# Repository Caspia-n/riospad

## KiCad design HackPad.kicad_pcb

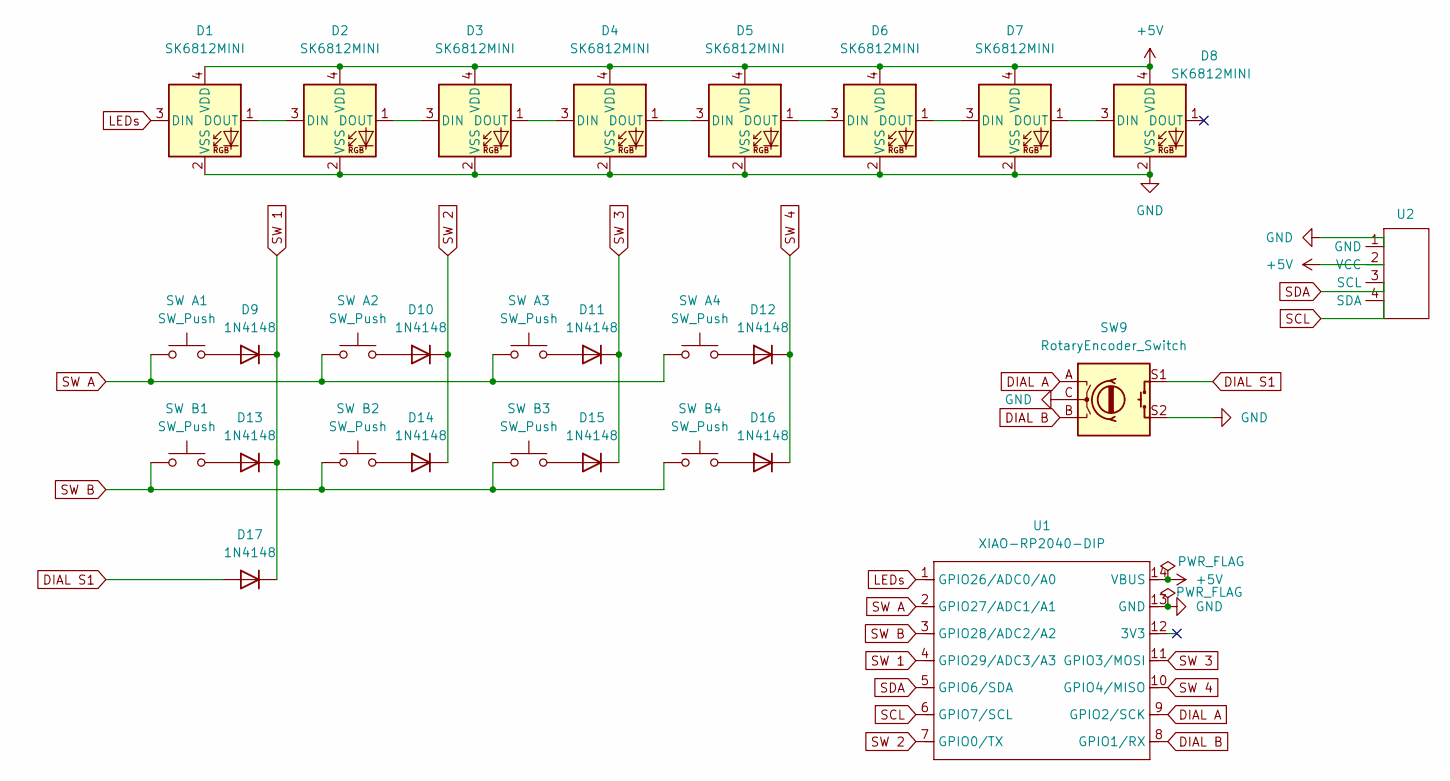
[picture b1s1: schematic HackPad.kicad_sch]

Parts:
D1, D2, D3, D4, D5, D6, D7, D8: SK6812MINI; LED_SK6812MINI_PLCC4_3.5x3.5mm_P1.75mm
D9, D10, D11, D12, D13, D14, D15, D16, D17: 1N4148; D_DO-35_SOD27_P7.62mm_Horizontal
SW9: RotaryEncoder_Switch; RotaryEncoder_Alps_EC12E-Switch_Vertical_H20mm
SW A1, SW A2, SW A3, SW A4: SW_Push; SW_Cherry_MX_1.00u_PCB
SW B1, SW B2, SW B3, SW B4: SW_Push; SW_Cherry_MX_1.00u_PCB
U1: XIAO-RP2040-DIP
U2: SSD1306-0.91-OLED-4pin-128x32

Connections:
+5V: D1.4 (VDD), D2.4 (VDD), D3.4 (VDD), D4.4 (VDD), D5.4 (VDD), D6.4 (VDD), D7.4 (VDD), D8.4 (VDD), U1.14 (VBUS), U2.2 (VCC)
DIAL A: SW9.A, U1.9 (GPIO2/SCK)
DIAL B: SW9.B, U1.8 (GPIO1/RX)
DIAL S1: D17.2 (A), SW9.S1
GND: D1.2 (VSS), D2.2 (VSS), D3.2 (VSS), D4.2 (VSS), D5.2 (VSS), D6.2 (VSS), D7.2 (VSS), D8.2 (VSS), SW9.C, SW9.S2, U1.13 (GND), U2.1 (GND)
LEDs: D1.3 (DIN), U1.1 (GPIO26/ADC0/A0)
unnamed: D1.1 (DOUT), D2.3 (DIN)
unnamed: D2.1 (DOUT), D3.3 (DIN)
unnamed: D3.1 (DOUT), D4.3 (DIN)
unnamed: D4.1 (DOUT), D5.3 (DIN)
unnamed: D5.1 (DOUT), D6.3 (DIN)
unnamed: D6.1 (DOUT), D7.3 (DIN)
unnamed: D7.1 (DOUT), D8.3 (DIN)
unnamed: D9.2 (A), SW A1.2
unnamed: D10.2 (A), SW A2.2
unnamed: D11.2 (A), SW A3.2
unnamed: D12.2 (A), SW A4.2
unnamed: D13.2 (A), SW B1.2
unnamed: D14.2 (A), SW B2.2
unnamed: D15.2 (A), SW B3.2
unnamed: D16.2 (A), SW B4.2
SCL: U1.6 (GPIO7/SCL), U2.4 (SDA)
SDA: U1.5 (GPIO6/SDA), U2.3 (SCL)
SW 1: D9.1 (K), D13.1 (K), D17.1 (K), U1.4 (GPIO29/ADC3/A3)
SW 2: D10.1 (K), D14.1 (K), U1.7 (GPIO0/TX)
SW 3: D11.1 (K), D15.1 (K), U1.11 (GPIO3/MOSI)
SW 4: D12.1 (K), D16.1 (K), U1.10 (GPIO4/MISO)
SW A: SW A1.1, SW A2.1, SW A3.1, SW A4.1, U1.2 (GPIO27/ADC1/A1)
SW B: SW B1.1, SW B2.1, SW B3.1, SW B4.1, U1.3 (GPIO28/ADC2/A2)

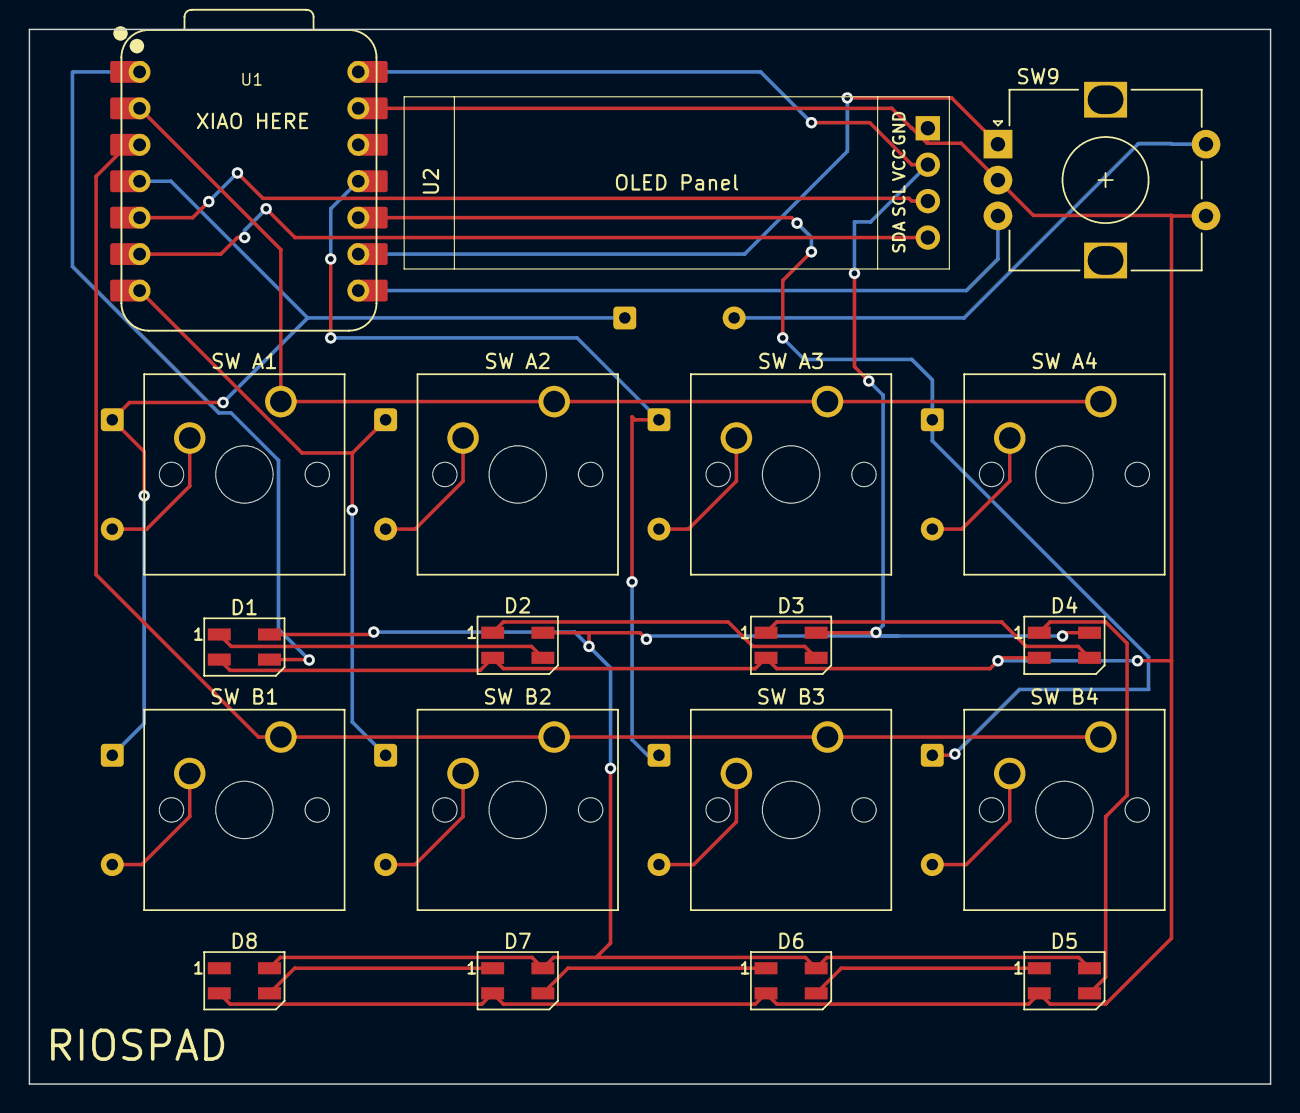
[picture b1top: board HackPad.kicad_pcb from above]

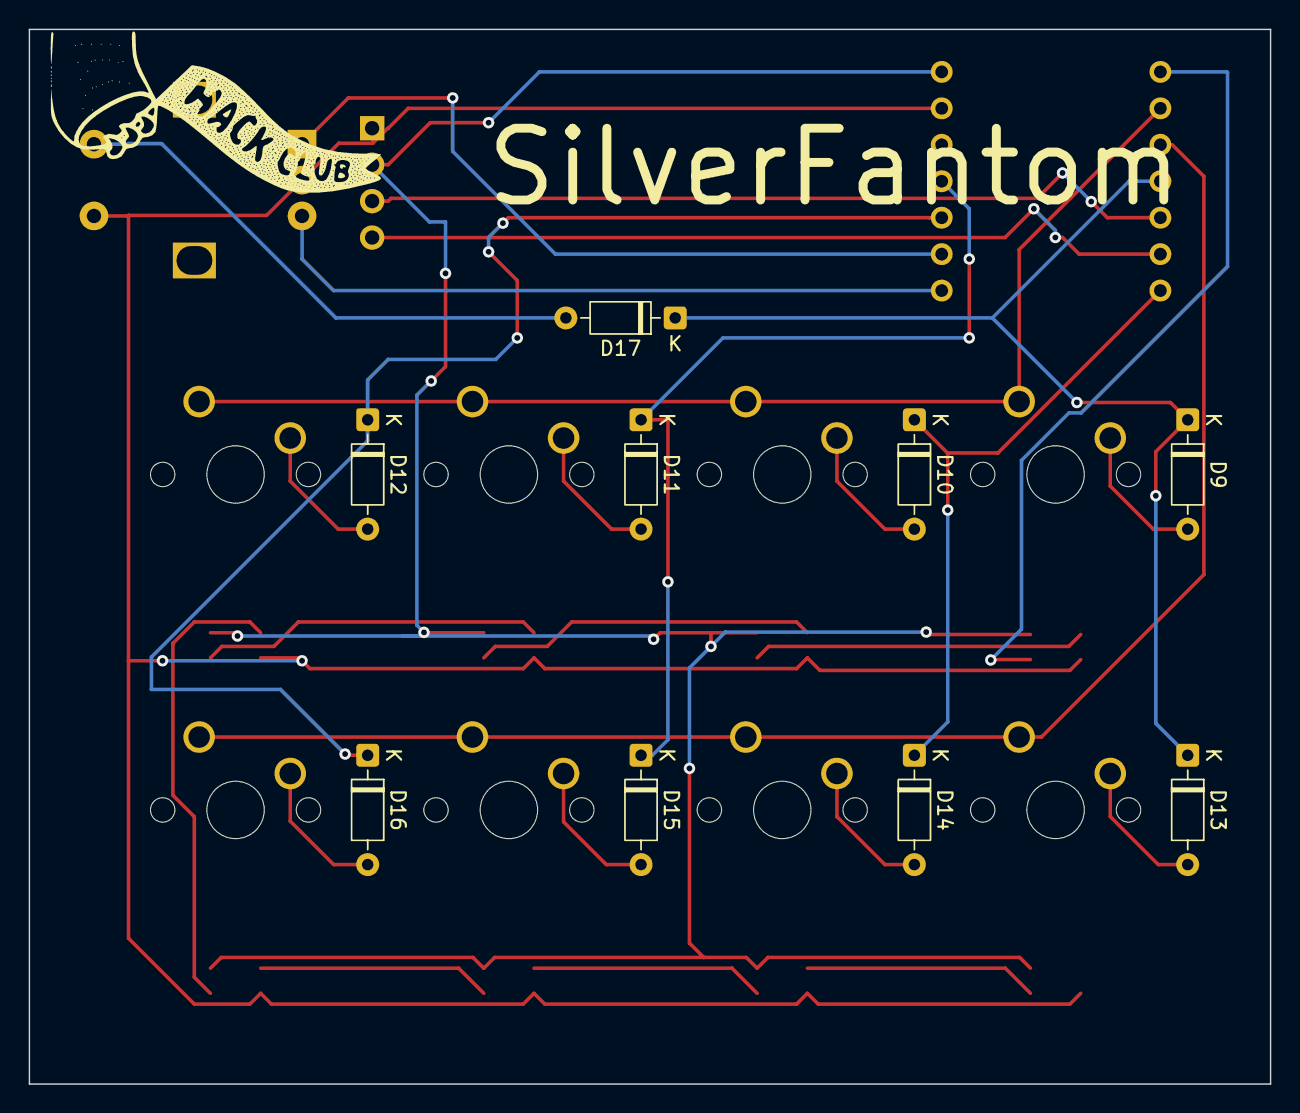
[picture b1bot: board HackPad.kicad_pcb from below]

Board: 2 copper layers, 86.5 x 73.5 mm, 28 parts (9 on the bottom side), 29 nets.

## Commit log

2025-12-05 Power pin
2025-12-05 Sketch done, busy with PCB
2025-12-06 diodes
2025-12-12 12/12
2025-12-20 19-12-2025
